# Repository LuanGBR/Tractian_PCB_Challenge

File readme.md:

# Tractian Technical Challenge

## The problem

Develop a full wireless communication system. 

**Requirements:**
- Send a file of size 500kB;
- The devices should be 100m apart open-air;
- At least  one of the devices must be battery powered.

## The solution

### 1. Sketch it up!

The first challenge was to choose the communication protocoto match the requeriments. Wi-Fi, Zig-Bee and bluetooth was considered, but LoRa has been chosen as the communication protocol. The main reason for this choice was the energy requirement, LoRa is extremely energy-efficient and also capable of sending a 500kB through a 100m gap in a resonable amount of time.

Doing some research about LoRa on IoT forums I dicovered a new product from Microchip, the SAM R34 module. It is a System In a Package that contains the microprocessor and the LoRa module in a single chip. Besides this advantages, I preferred this solution because I've already make other projects with Microchips products., and i've had good impressions.

<!-- imagem do chip -->

The next step was to dive deep into the SiP Datasheet and documentation, to understand the specificities of this microprocessor. After that I was capable of sketching a schematic. It is in the repository named  <!-- nome do arquivo -->

**Microcontroller**

**RF circuit**

**Oscillators**

**learnings:**

- When dealing with RF circuits it is import to add some decoupling capacitors to minimize interference, they act as low-pass filters and is import to place it right next to the chip terminals

### 2. It’s layout time
 
With the schematic on hand the PCB project started. As PCB design guidelines (and the SAMR34 datasheet) suggest boards with analog electronic, specially RF electronic, should be at least 4 layers, one being a ground plane, another being the power layer. Also, it's good to physically apart the components by their function, specially the RF components that can suffer from interference. 

#### Controlled Impedance
To reduce reflectance of the signal on analog signal tracks it is import to tune the track impedance to match the internals of the RF module and antenna. In this implementation, 50$\Omega$. 

For reference, the PCB dimensions and tolerances are from JCLPCB JLC7628 Stackup.

|  Min. Trace width/Spacing  | Min. Via  |   Min. BGA |
|---:|---:|---:|
|3.5mil|0.2mm|0.25mm

**Prepeg/Core dieletric constant:**  4.6

**Stacking:**
| Layer         | Material Type | Thickness |
|---------------|---------------|-----------|
| Top Layer1    | Copper        | 0.035 mm  |
| Prepreg       | 7628*1        | 0.2104 mm |
| Inner Layer2  | Copper        | 0.0152 mm |
| Core          | Core          | 1.065 mm  |
| Inner Layer3  | Copper        | 0.0152 mm |
| Prepreg       | 7628*1        | 0.2104 mm |
| Bottom Layer4 | Copper        | 0.035 mm  |
| **Total**| --|1.5862 mm|

Therefore, all RF tracks were made with this tuned impedance in mind.

#### Final Result

**Layers except GND plane**

**3D view**

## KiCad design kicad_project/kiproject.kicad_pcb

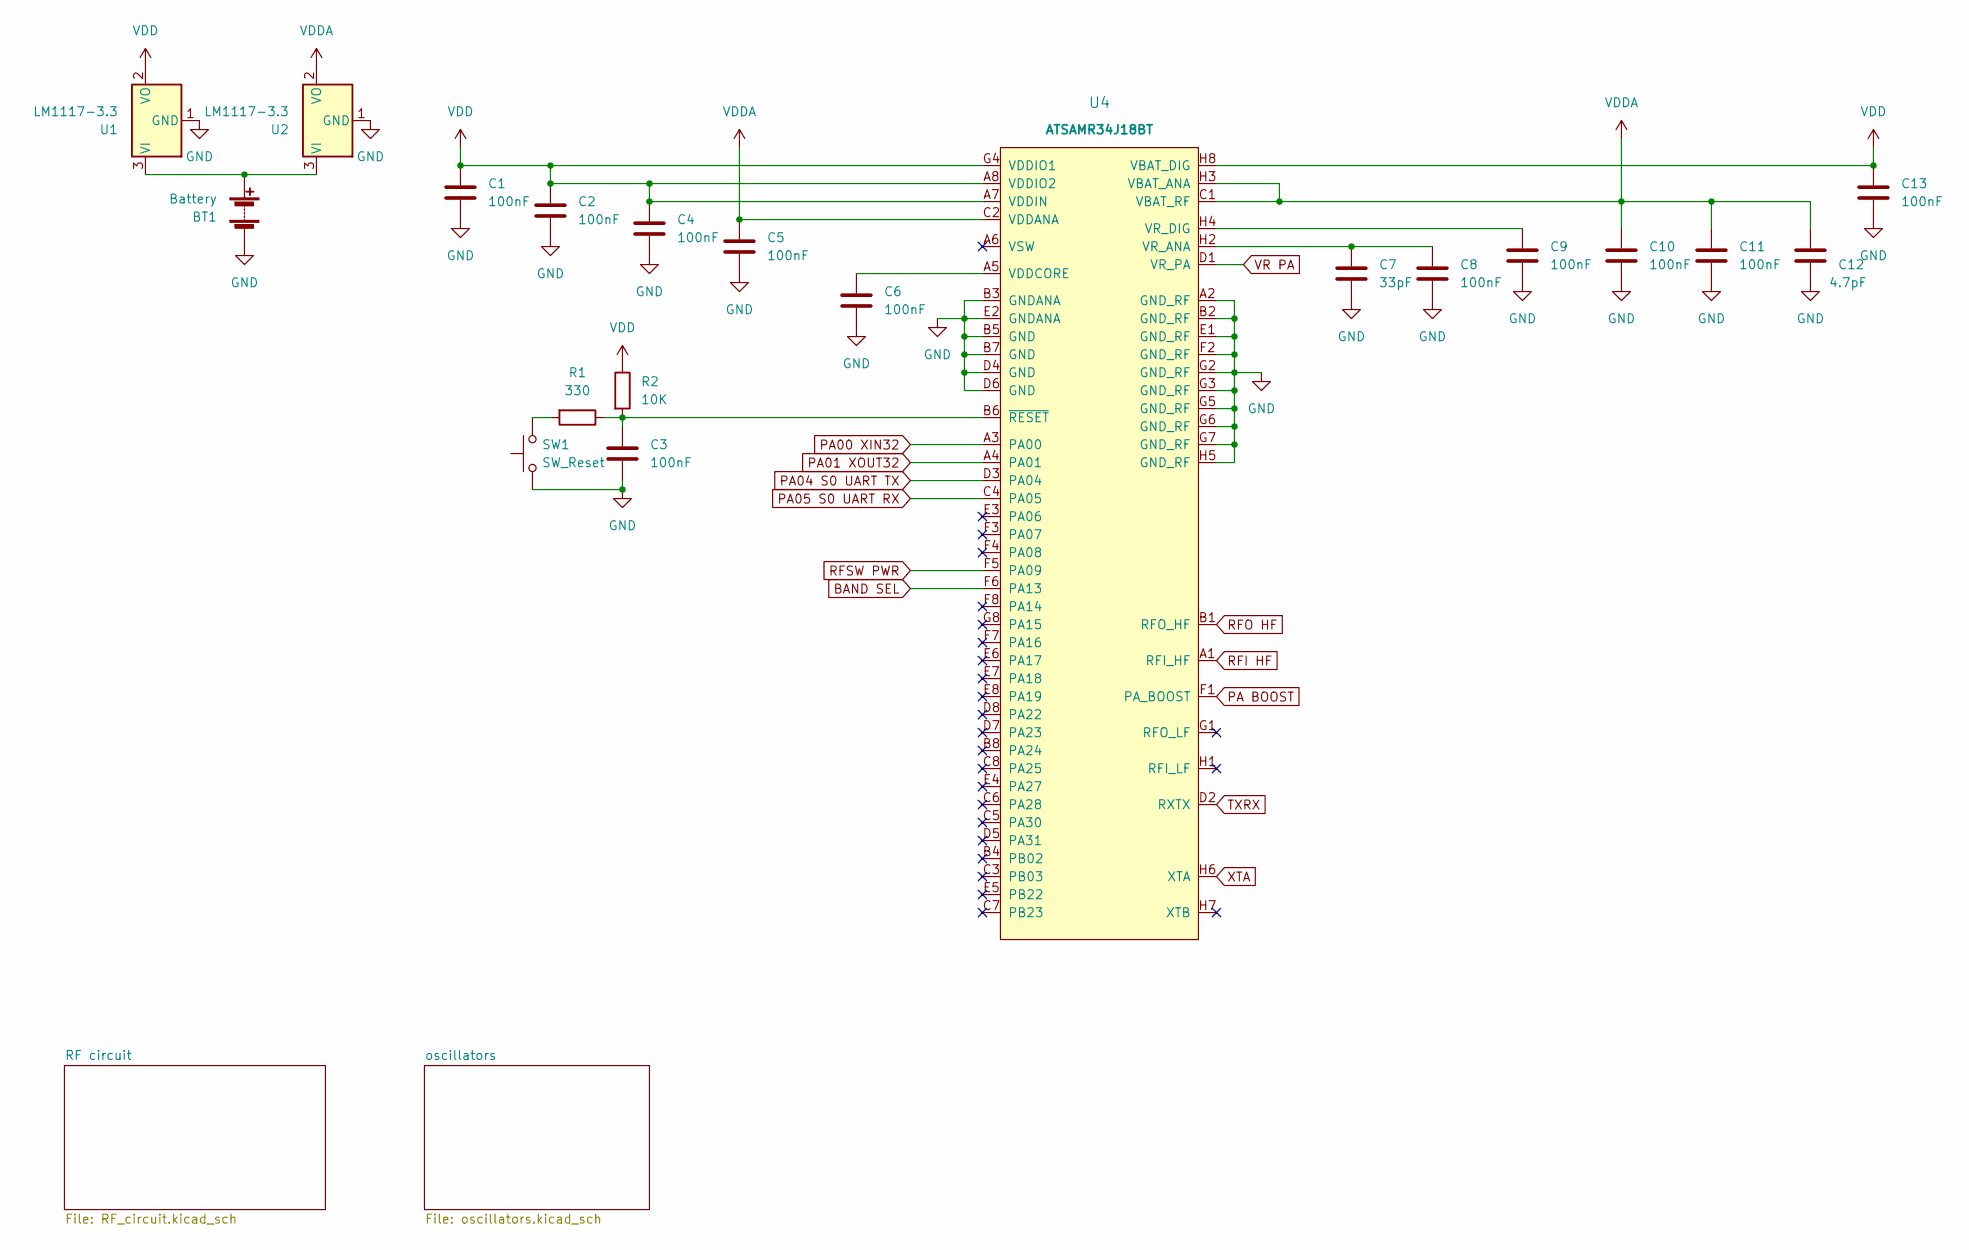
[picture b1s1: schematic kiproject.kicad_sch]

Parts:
BT1: Battery; BatteryHolder_Eagle_12BH611-GR
C1, C2, C3, C4, C5, C6, C8, C9, C10, C11, C13: 100nF; C_0201_0603Metric
C7: 33pF; C_0201_0603Metric
C12: 4.7pF; C_0201_0603Metric
R1: 330; C_0402_1005Metric
R2: 10K; C_0402_1005Metric
SW1: SW_Reset; SW_PUSH_6mm
U1, U2: LM1117-3.3; TO254P470X1016X2222-3P
U4: ATSAMR34J18BT; ATSAMR34J18BT-I&slash_7JX

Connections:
BAND SEL: U4.F6 (PA13); also elsewhere on the board
GND: BT1.2 (-), C1.2, C2.2, C3.2, C4.2, C5.2, C6.2, C7.2, C8.2, C9.2, C10.2, C11.2, C12.2, C13.2, SW1.1, U1.1 (GND), U2.1 (GND), U4.A2 (GND_RF), U4.B2 (GND_RF), U4.B3 (GNDANA), U4.B5 (GND), U4.B7 (GND), U4.D4 (GND), U4.D6 (GND), U4.E1 (GND_RF), U4.E2 (GNDANA), U4.F2 (GND_RF), U4.G2 (GND_RF), U4.G3 (GND_RF), U4.G5 (GND_RF), U4.G6 (GND_RF), U4.G7 (GND_RF), U4.H5 (GND_RF); also elsewhere on the board
unnamed: BT1.1 (+), U1.3 (VI), U2.3 (VI)
unnamed: C3.1, R1.1, R2.2, U4.B6 (~RESET)
unnamed: C6.1, U4.A5 (VDDCORE)
unnamed: C7.1, C8.1, U4.H2 (VR_ANA)
unnamed: C9.1, U4.H4 (VR_DIG)
unnamed: R1.2, SW1.2
PA00 XIN32: U4.A3 (PA00); also elsewhere on the board
PA01 XOUT32: U4.A4 (PA01); also elsewhere on the board
PA04 S0 UART TX: U4.D3 (PA04)
PA05 S0 UART RX: U4.C4 (PA05)
PA BOOST: U4.F1 (PA_BOOST); also elsewhere on the board
RFI HF: U4.A1 (RFI_HF); also elsewhere on the board
RFO HF: U4.B1 (RFO_HF); also elsewhere on the board
RFSW PWR: U4.F5 (PA09); also elsewhere on the board
TXRX: U4.D2 (RXTX); also elsewhere on the board
VDD: C1.1, C2.1, C4.1, C13.1, R2.1, U1.2 (VO), U4.A7 (VDDIN), U4.A8 (VDDIO2), U4.G4 (VDDIO1), U4.H8 (VBAT_DIG)
VDDA: C5.1, C10.1, C11.1, C12.1, U2.2 (VO), U4.C1 (VBAT_RF), U4.C2 (VDDANA), U4.H3 (VBAT_ANA)
VR PA: U4.D1 (VR_PA); also elsewhere on the board
XTA: U4.H6 (XTA); also elsewhere on the board

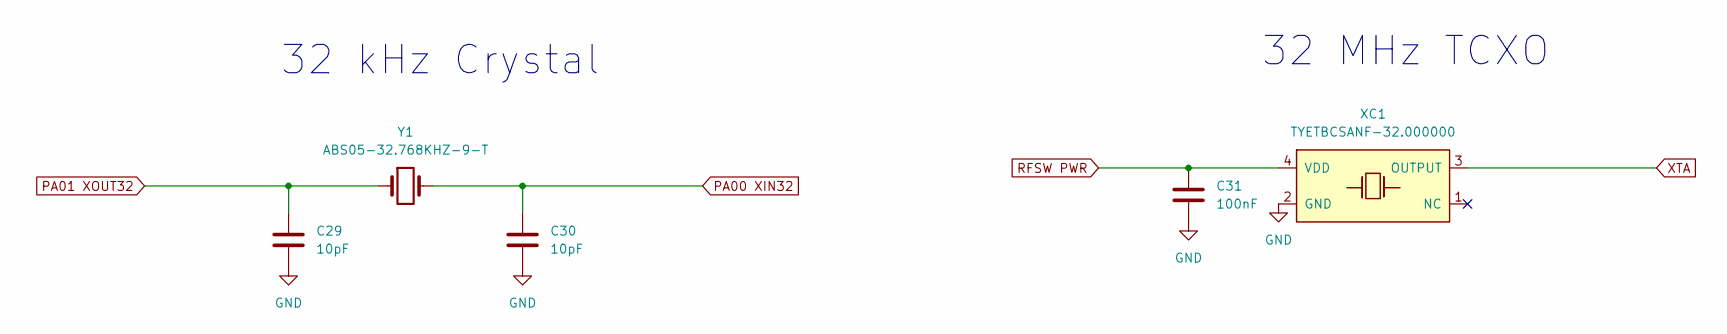
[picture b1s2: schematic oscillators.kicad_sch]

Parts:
C29, C30: 10pF; C_0201_0603Metric
C31: 100nF; C_0603_1608Metric
XC1: TYETBCSANF-32.000000; Oscilator_2.5x2.0
Y1: ABS05-32.768KHZ-9-T; ABS0532768KHZ9T

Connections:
GND: C29.2, C30.2, C31.2, XC1.2 (GND); also elsewhere on the board
PA00 XIN32: C30.1, Y1.2; also elsewhere on the board
PA01 XOUT32: C29.1, Y1.1; also elsewhere on the board
RFSW PWR: C31.1, XC1.4 (VDD); also elsewhere on the board
XTA: XC1.3 (OUTPUT); also elsewhere on the board

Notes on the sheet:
32 kHz Crystal
32 MHz TCXO

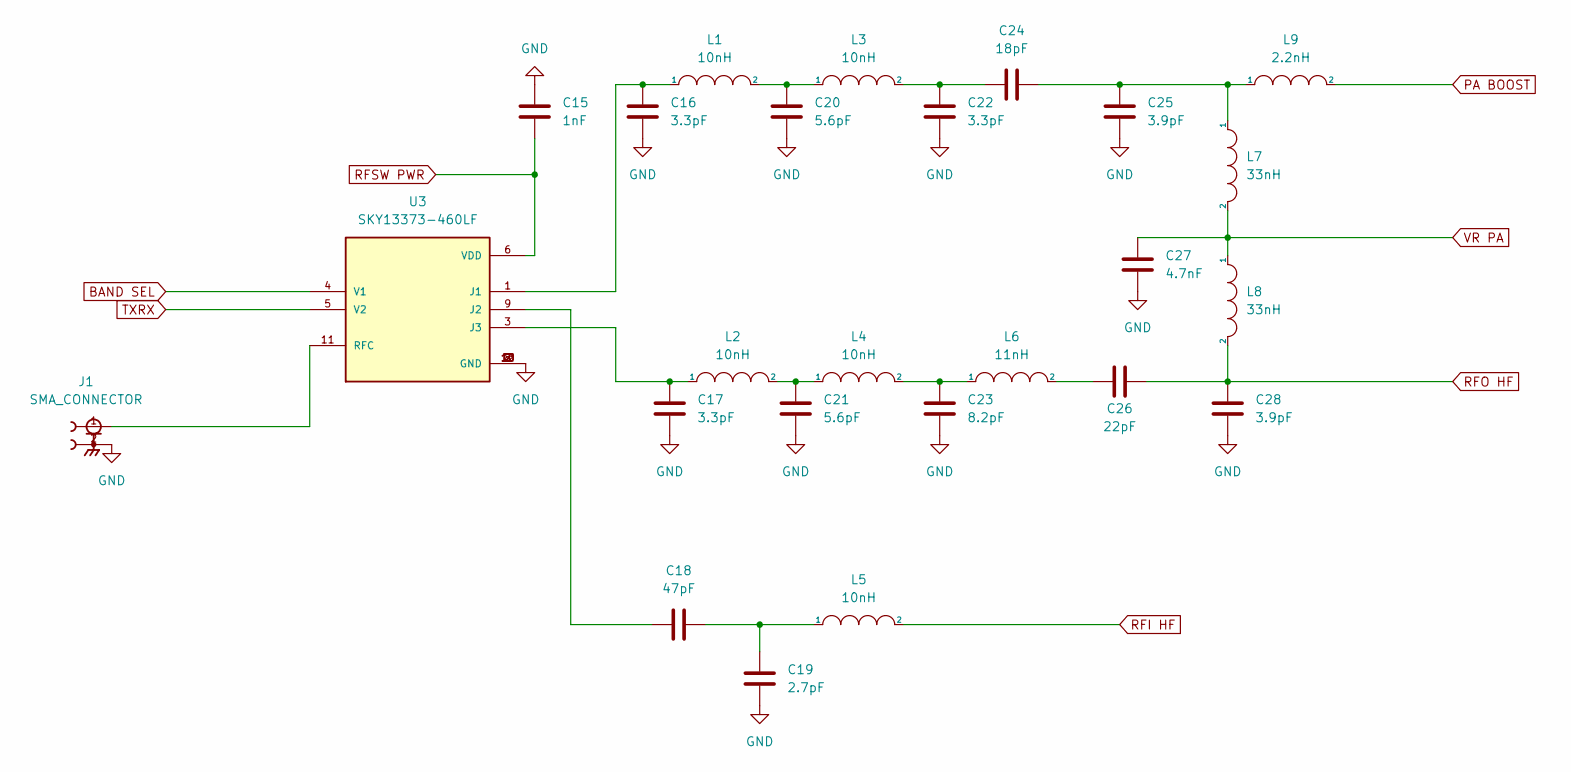
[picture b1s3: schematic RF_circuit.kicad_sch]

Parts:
C15: 1nF; C_0201_0603Metric
C16, C17, C22: 3.3pF; C_0201_0603Metric
C18: 47pF; C_0201_0603Metric
C19: 2.7pF; C_0201_0603Metric
C20, C21: 5.6pF; C_0201_0603Metric
C23: 8.2pF; C_0201_0603Metric
C24: 18pF; C_0201_0603Metric
C25, C28: 3.9pF; C_0201_0603Metric
C26: 22pF; C_0201_0603Metric
C27: 4.7nF; C_0201_0603Metric
J1: SMA_CONNECTOR; SMA_J_P_X_ST_EM1_EdgeMount; PARTREV 1.3
L1, L2, L3, L4, L5: 10nH; L_0201_0603Metric
L6: 11nH; L_0201_0603Metric
L7, L8: 33nH; L_0201_0603Metric
L9: 2.2nH; L_0201_0603Metric
U3: SKY13373-460LF; QFN50P200X200X65-13N; PARTREV May 6, 2016

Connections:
BAND SEL: U3.4 (V1); also elsewhere on the board
GND: C15.2, C16.2, C17.2, C19.2, C20.2, C21.2, C22.2, C23.2, C25.2, C27.2, C28.2, J1.2, U3.2 (GND), U3.7 (GND), U3.8 (GND), U3.10 (GND), U3.12 (GND), U3.13 (GND); also elsewhere on the board
unnamed: C16.1, L1.1, U3.1 (J1)
unnamed: C17.1, L2.1, U3.3 (J3)
unnamed: C18.1, U3.9 (J2)
unnamed: C18.2, C19.1, L5.1
unnamed: C20.1, L1.2, L3.1
unnamed: C21.1, L2.2, L4.1
unnamed: C22.1, C24.1, L3.2
unnamed: C23.1, L4.2, L6.1
unnamed: C24.2, C25.1, L7.1, L9.1
unnamed: C26.1, L6.2
unnamed: J1.1, U3.11 (RFC)
PA BOOST: L9.2; also elsewhere on the board
RFI HF: L5.2; also elsewhere on the board
RFO HF: C26.2, C28.1, L8.2; also elsewhere on the board
RFSW PWR: C15.1, U3.6 (VDD); also elsewhere on the board
TXRX: U3.5 (V2); also elsewhere on the board
VR PA: C27.1, L7.2, L8.1; also elsewhere on the board

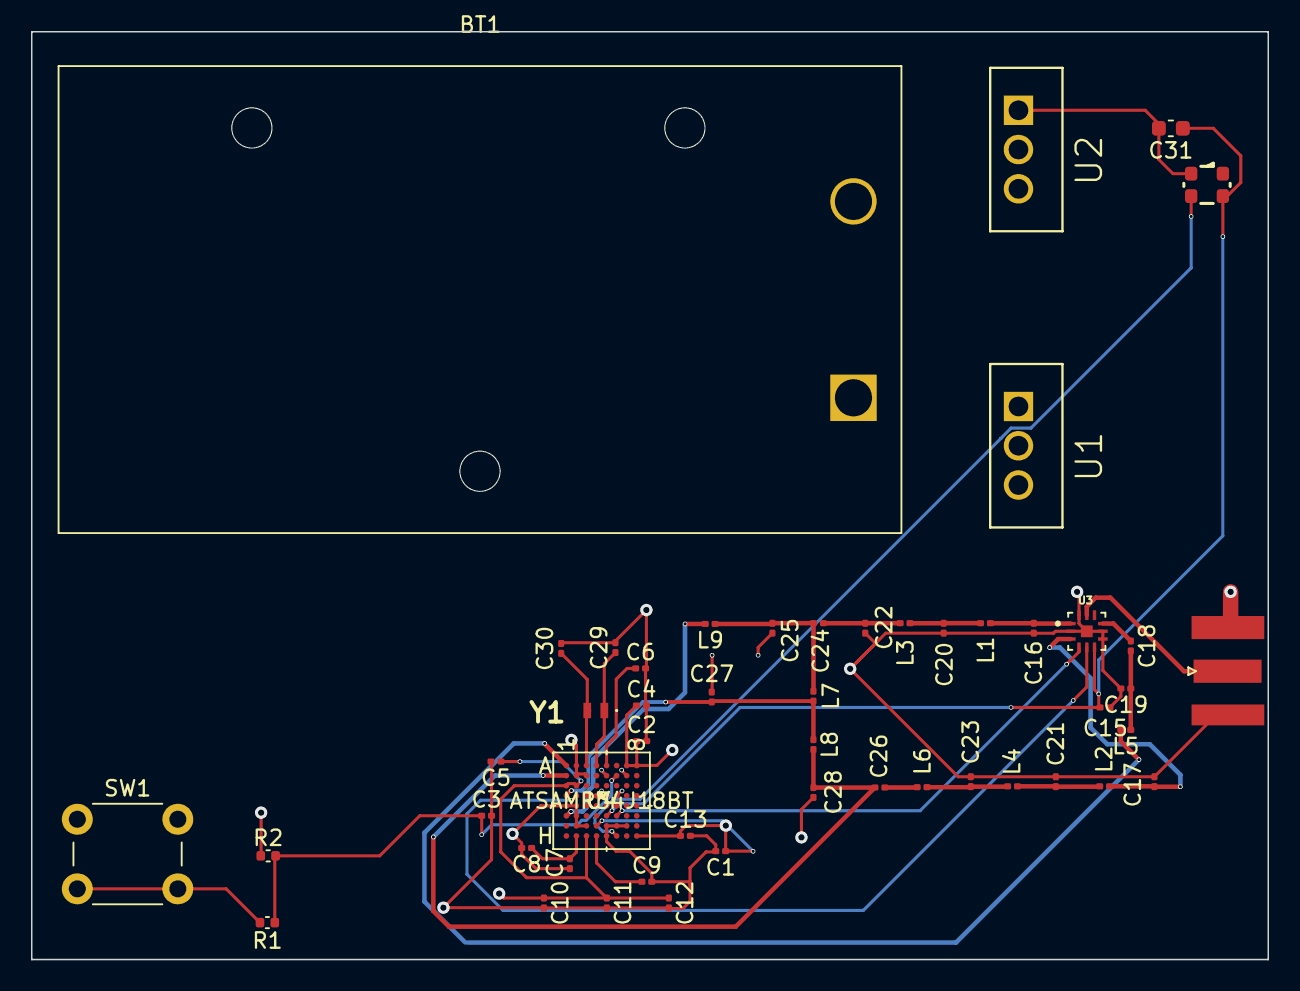
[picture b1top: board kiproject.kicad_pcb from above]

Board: 4 copper layers, 80.0 x 60.0 mm, 50 parts (0 on the bottom side), 30 nets.

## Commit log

2022-12-19 init commit

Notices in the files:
parts and their libraries:
Copyright 2021 Accelerated Designs. All rights reserved.
